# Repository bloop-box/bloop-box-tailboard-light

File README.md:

# Bloop Box Tailboard Light

[Documentation](https://bloop-box.github.io/bloop-box-tailboard-light)

The board is designed using KiCAD 6 with production and assembly by JLCPCB in mind. All parts are selected to be
available from JLCPCB. At the time of writing as many parts as possible are used from their basic library.

- USB-C Power Input
- 5V only
- Two buttons connected to the Raspberry Pi, per default used for volume control
- Three LEDs 
  - One to show status of power supply
  - Two can be remote-controlled by Raspberry Pi through the Mainboard

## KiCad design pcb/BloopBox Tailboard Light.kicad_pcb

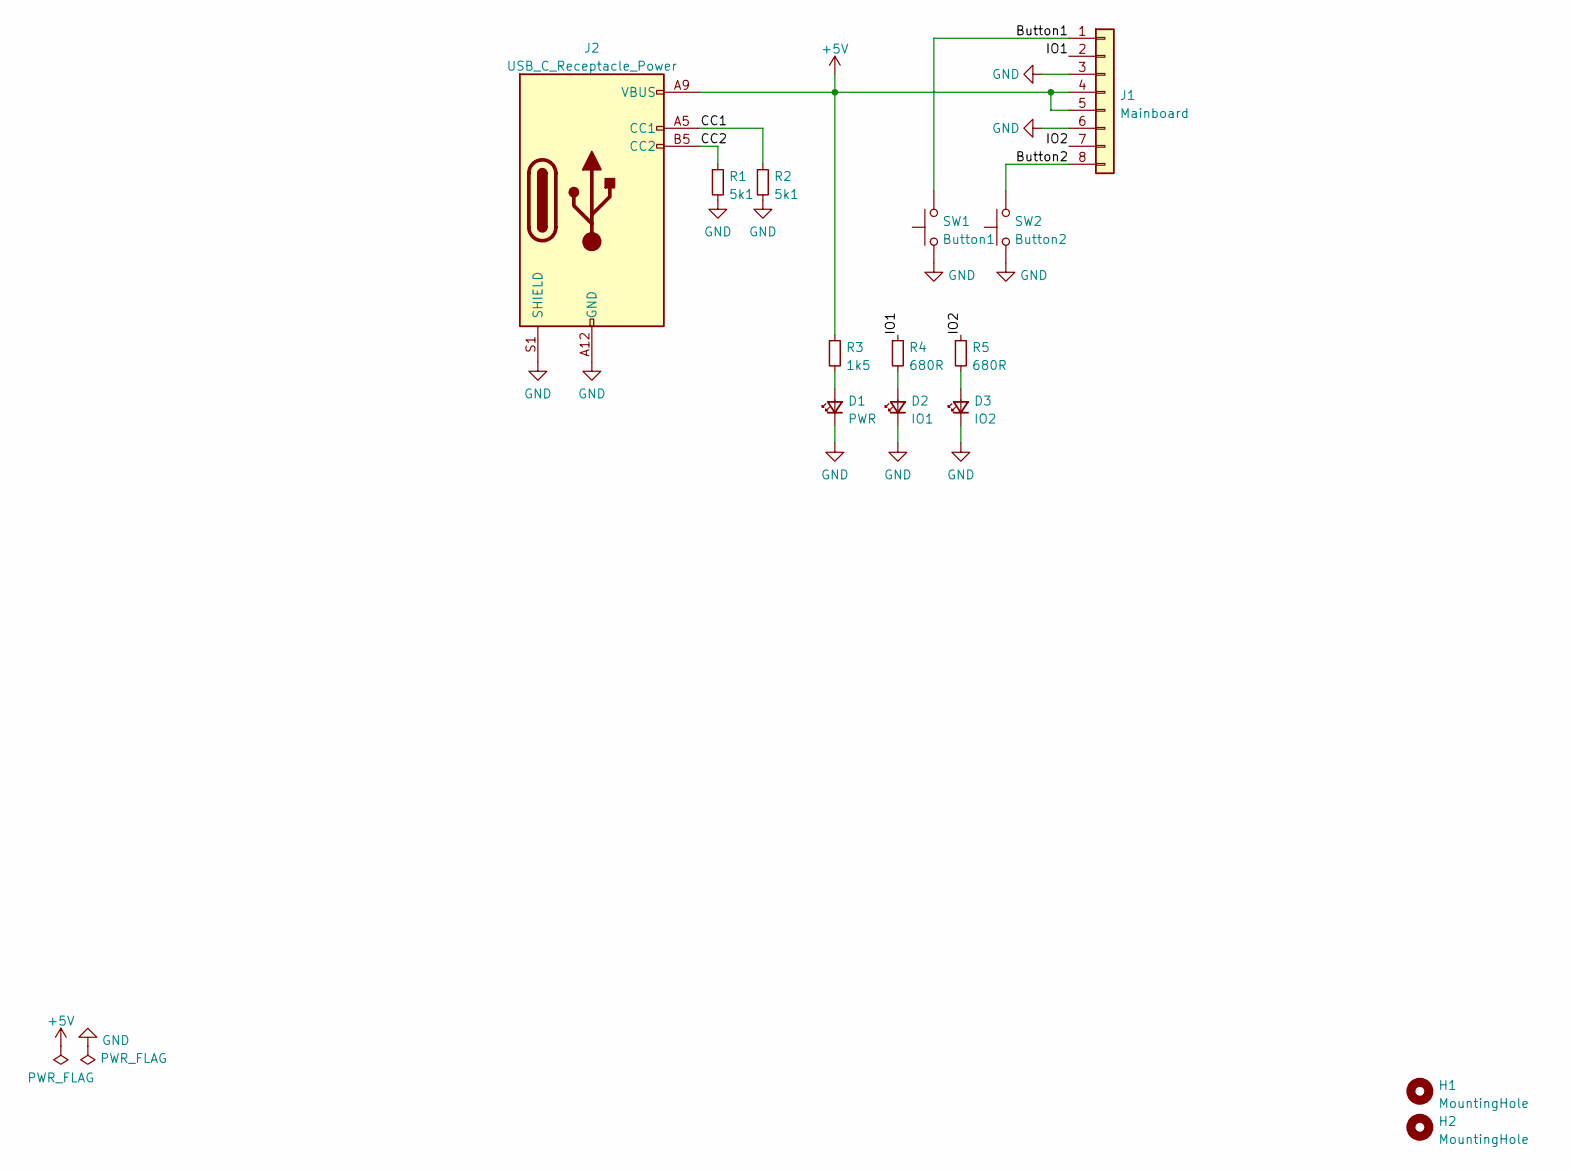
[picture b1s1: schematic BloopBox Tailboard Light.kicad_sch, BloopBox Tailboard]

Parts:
D1: PWR; LED_0603_1608Metric; LCSC C72038
D2: IO1; LED_0603_1608Metric; LCSC C72038
D3: IO2; LED_0603_1608Metric; LCSC C72038
H1, H2: MountingHole; MountingHole_3.2mm_M3
J1: Mainboard; JST_PH_S8B-PH-K_1x08_P2.00mm_Horizontal; LCSC C20598766
J2: USB_C_Receptacle_Power; GCT_USB4125-GF-A_REVA2; LCSC C283540
R1, R2: 5k1; R_0603_1608Metric; LCSC C23186
R3: 1k5; R_0603_1608Metric; LCSC C22843
R4, R5: 680R; R_0603_1608Metric; LCSC C23228
SW1: Button1; SW_Tactile_SPST_Angled_PTS645Vx83-2LFS; LCSC C338650
SW2: Button2; SW_Tactile_SPST_Angled_PTS645Vx83-2LFS; LCSC C338650

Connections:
+5V: J1.4, J1.5, J2.A9 (VBUS), J2.B9 (VBUS), R3.1
/Button1: J1.1, SW1.2
/Button2: J1.8, SW2.2
/CC1: J2.A5 (CC1), R2.1
/CC2: J2.B5 (CC2), R1.1
/IO1: J1.2, R4.1
/IO2: J1.7, R5.1
GND: D1.1 (K), D2.1 (K), D3.1 (K), J1.3, J1.6, J2.A12 (GND), J2.B12 (GND), J2.S1 (SHIELD), R1.2, R2.2, SW1.1, SW2.1
unnamed: D1.2 (A), R3.2
unnamed: D2.2 (A), R4.2
unnamed: D3.2 (A), R5.2

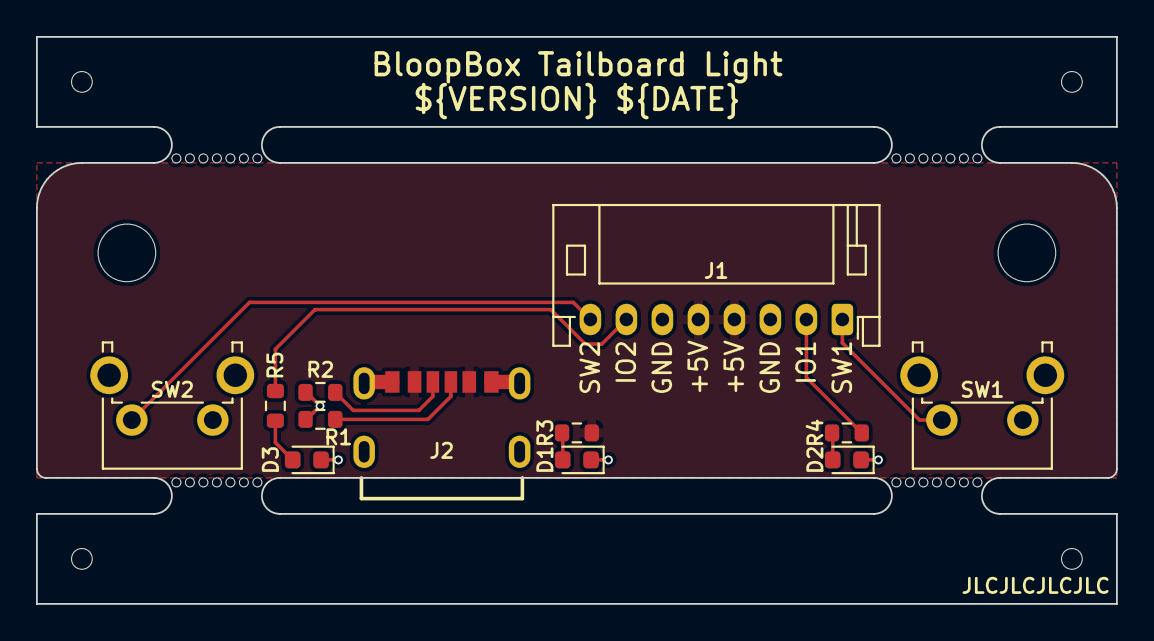
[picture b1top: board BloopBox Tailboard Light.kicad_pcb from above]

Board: 2 copper layers, 60.0 x 31.5 mm, 18 parts (0 on the bottom side), 11 nets.

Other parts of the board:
mouse-bite-2mm-slot, mouse-bite-2mm-slot#2, mouse-bite-2mm-slot#3, mouse-bite-2mm-slot#4: VAL**; mouse-bite-2x5mm-slot-onesided

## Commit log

2022-12-11 chore: fork Tailboard Repository
    Fork of BloopBox Tailboard for the light version
2022-12-11 feat: remove active circuitry from PCB
2022-12-11 fix: remove unused net
2022-12-11 feat: remove active circuitry from schematics
    Removing all active circuitry from the light-version of the Tailboard
2022-12-11 fix: change resistors to 0603 footptint
    Changing the resistor footprints to 0603 to make hand-soldering easier, since this board does not have the size restraints of the full version of the Tailboard
2022-12-11 chore(main): release 1.0.0
2024-08-14 chore: update to KiCad 8
2024-08-14 fix: part number for connector
2024-08-14 chore(main): release 1.0.1
2024-08-29 ci: remove dependency between jobs
